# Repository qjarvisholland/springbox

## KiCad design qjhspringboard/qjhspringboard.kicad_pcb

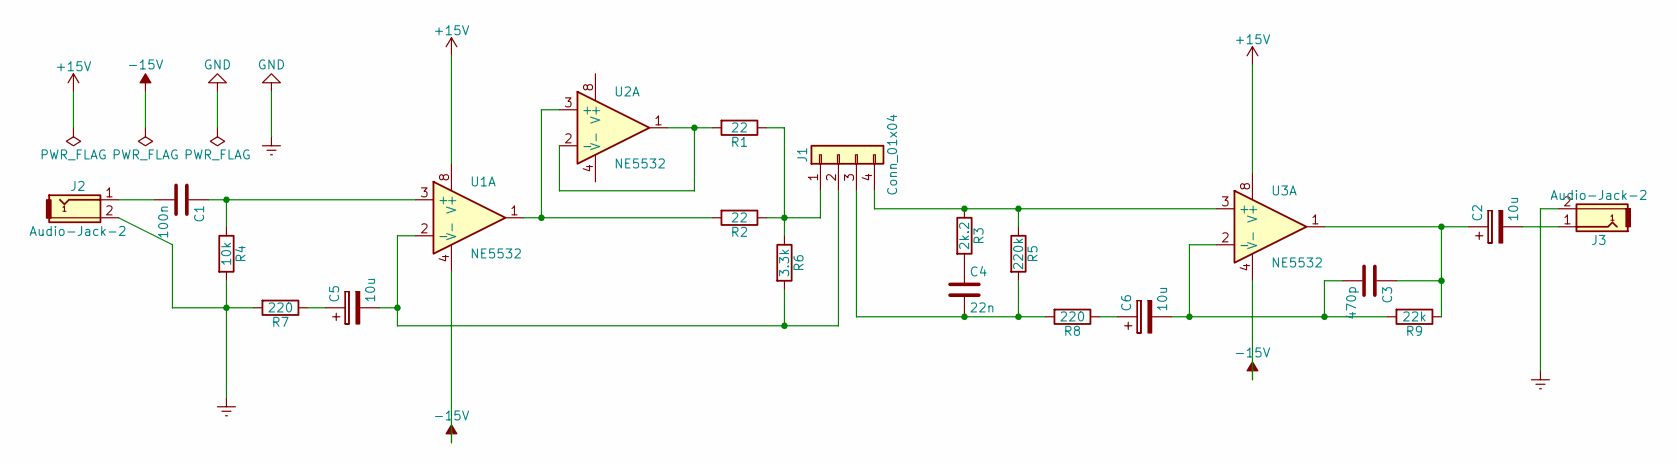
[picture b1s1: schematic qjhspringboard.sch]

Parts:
C1: 100n; C_Disc_D3.8mm_W2.6mm_P2.50mm
C2, C5, C6: 10u; CP_Radial_D5.0mm_P2.50mm
C3: 470p; C_0603_HandSoldering
C4: 22n; C_Disc_D3.8mm_W2.6mm_P2.50mm
J1: Conn_01x04; Pin_Header_Straight_1x04_Pitch2.00mm
J2, J3: Audio-Jack-2; Pin_Header_Straight_1x02_Pitch2.00mm
R1, R2: 22; R_Axial_DIN0204_L3.6mm_D1.6mm_P7.62mm_Horizontal
R3: 2k.2; R_Axial_DIN0204_L3.6mm_D1.6mm_P7.62mm_Horizontal
R4: 10k; R_Axial_DIN0204_L3.6mm_D1.6mm_P7.62mm_Horizontal
R5: 220k; R_Axial_DIN0204_L3.6mm_D1.6mm_P7.62mm_Horizontal
R6: 3.3k; R_Axial_DIN0204_L3.6mm_D1.6mm_P7.62mm_Horizontal
R7, R8: 220; R_Axial_DIN0204_L3.6mm_D1.6mm_P7.62mm_Horizontal
R9: 22k; R_Axial_DIN0204_L3.6mm_D1.6mm_P7.62mm_Horizontal
U1, U2, U3: NE5532; SOIC-8-N

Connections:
+15V: U1.8 (V+), U3.8 (V+)
-15V: U1.4 (V-), U3.4 (V-)
Earth: J2.2, J3.2, R4.2, R7.2
unnamed: C1.1, R4.1, U1.3 (+)
unnamed: C1.2, J2.1
unnamed: C2.1, C3.1, R9.1, U3.1
unnamed: C2.2, J3.1
unnamed: C3.2, C6.2, R9.2, U3.2 (-)
unnamed: C4.1, R3.2
unnamed: C4.2, J1.3, R5.2, R8.2
unnamed: C5.1, R7.1
unnamed: C5.2, J1.2, R6.2, U1.2 (-)
unnamed: C6.1, R8.1
unnamed: J1.1, R1.1, R2.1, R6.1
unnamed: J1.4, R3.1, R5.1, U3.3 (+)
unnamed: R1.2, U2.1, U2.2 (-)
unnamed: R2.2, U1.1, U2.3 (+)

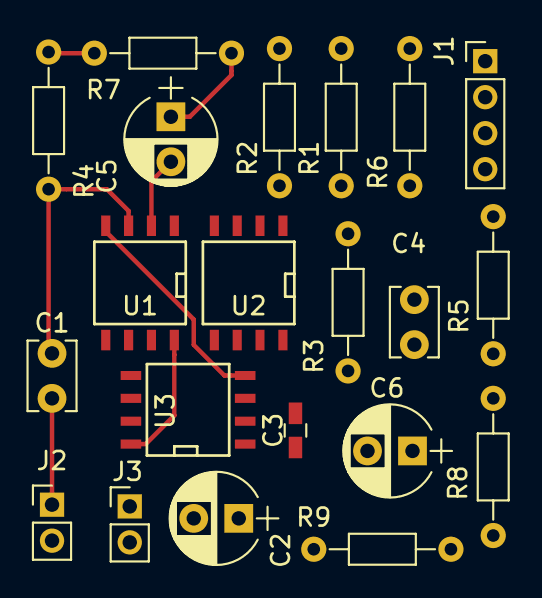
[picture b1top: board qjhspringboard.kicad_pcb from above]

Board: 2 copper layers, 21 parts (0 on the bottom side), 17 nets.

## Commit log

2019-03-14 added proto schematic files
2019-03-14 other kicad project file
2019-04-28 schematic is finished other than power connections, pcb layout started and some wiring done, needs power connectors for 15+/-
2019-04-28 including files from pcblayout as before, still needs power connectors
